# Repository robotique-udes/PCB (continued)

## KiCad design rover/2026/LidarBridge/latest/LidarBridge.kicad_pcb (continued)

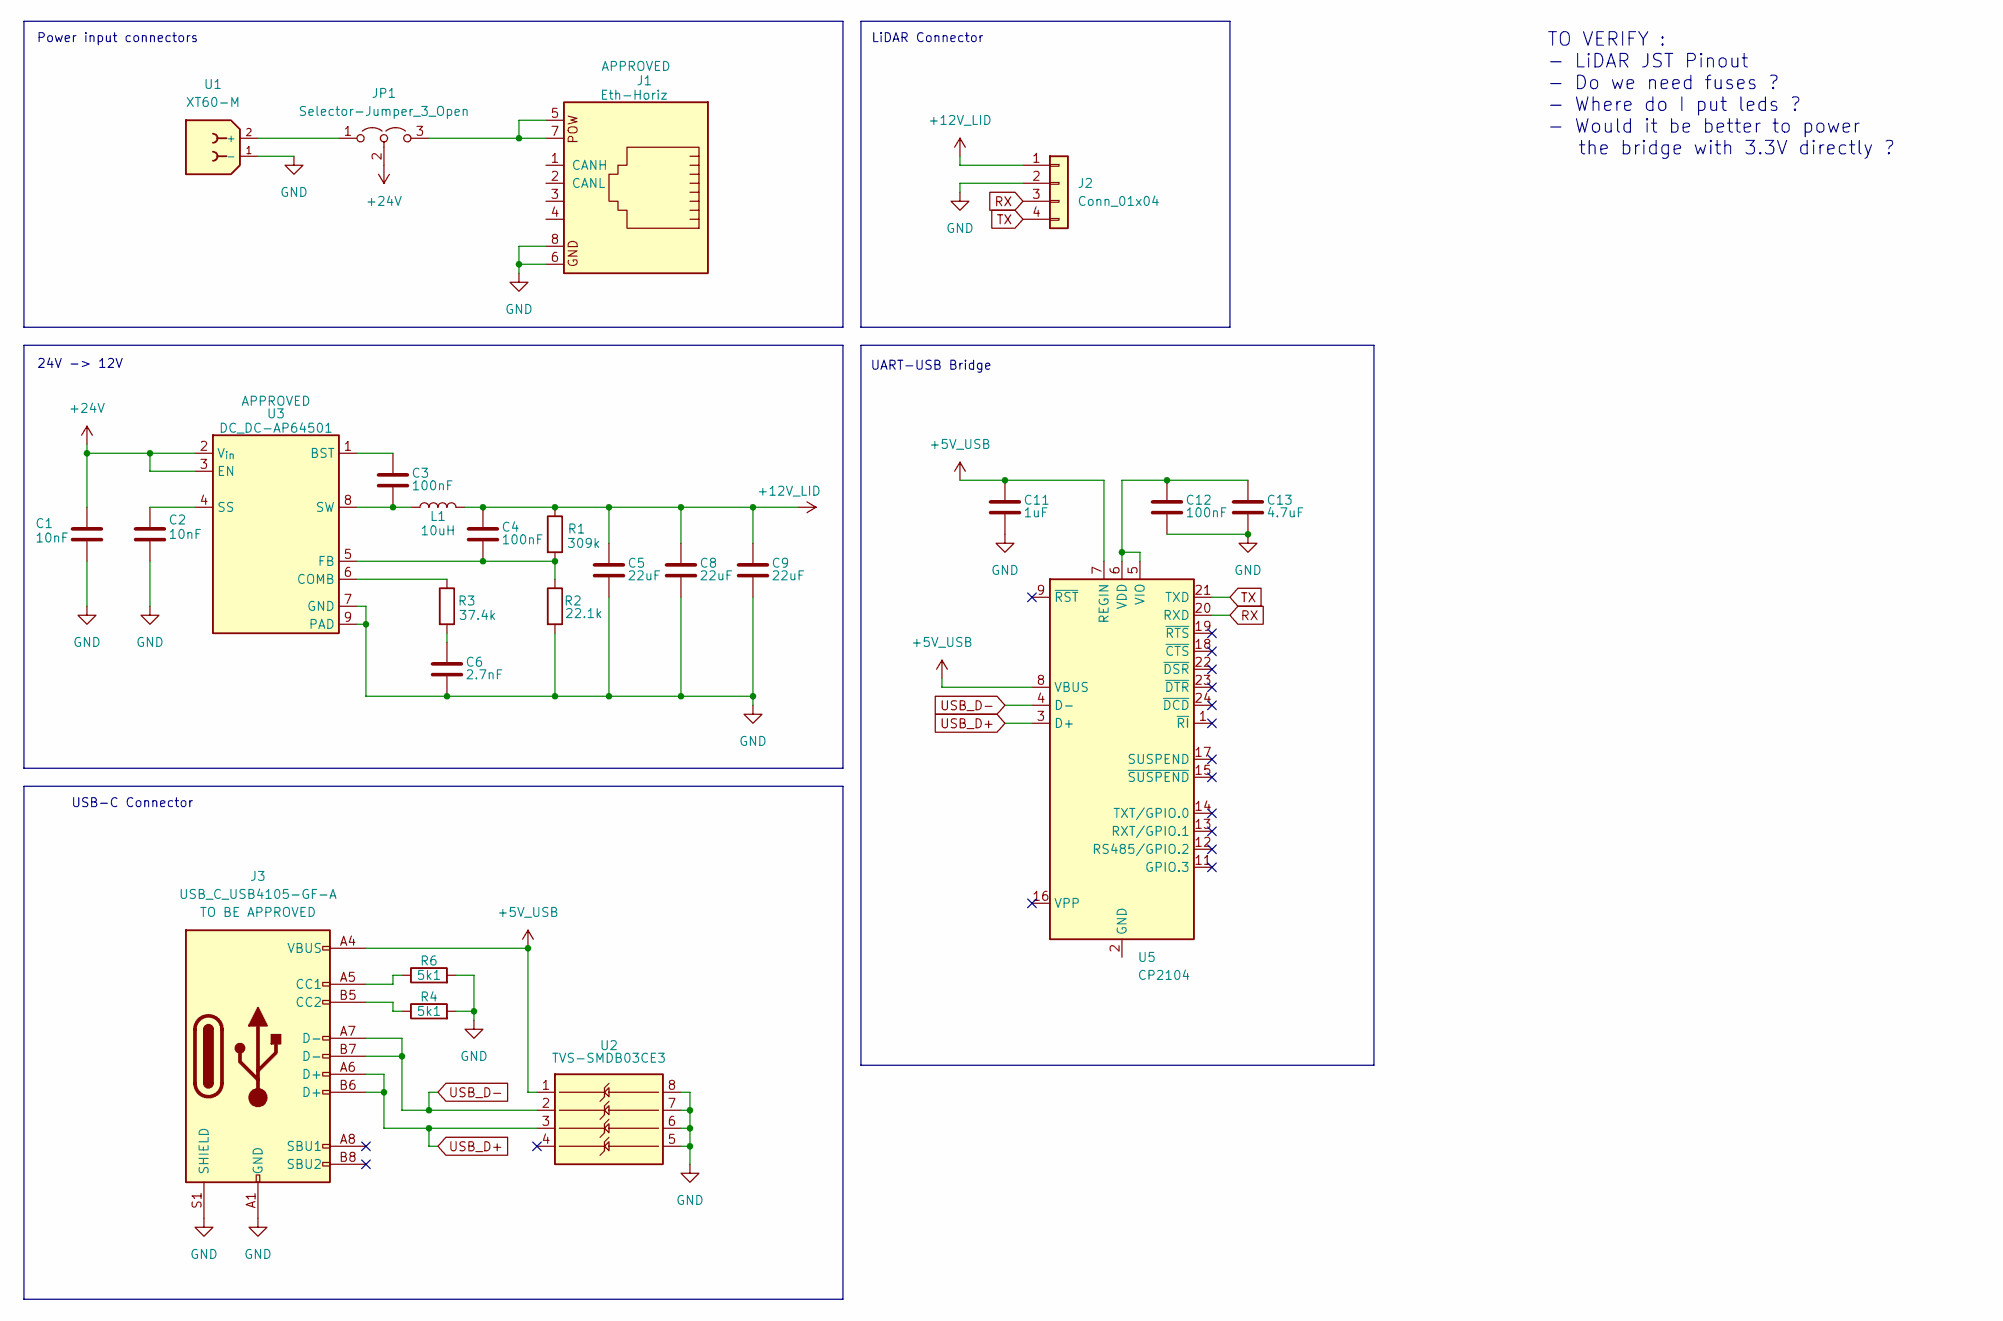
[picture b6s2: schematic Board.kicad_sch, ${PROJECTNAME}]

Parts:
C1, C2: 10nF; C_0805_2012Metric_Pad1.18x1.45mm_HandSolder
C3, C4, C12: 100nF; C_0805_2012Metric_Pad1.18x1.45mm_HandSolder
C5, C8, C9: 22uF; C_0805_2012Metric_Pad1.18x1.45mm_HandSolder
C6: 2.7nF; C_0805_2012Metric_Pad1.18x1.45mm_HandSolder
C11: 1uF; C_0805_2012Metric_Pad1.18x1.45mm_HandSolder
C13: 4.7uF; C_0805_2012Metric_Pad1.18x1.45mm_HandSolder
J1: Eth-Horiz; Ethernet_Horizontal
J2: Conn_01x04; JST_PH_B4B-PH-K_1x04_P2.00mm_Vertical
J3: USB_C_USB4105-GF-A; USB_C_Receptacle_GCT_USB4105-xx-A_16P_TopMnt_Horizontal
JP1: Selector-Jumper_3_Open; PinHeader_1x03_P2.54mm_Vertical
L1: 10uH; L_3.6u_ASPI-6045S-3R6N-T
R1: 309k; R_0805_2012Metric_Pad1.20x1.40mm_HandSolder
R2: 22.1k; R_0805_2012Metric_Pad1.20x1.40mm_HandSolder
R3: 37.4k; R_0805_2012Metric_Pad1.20x1.40mm_HandSolder
R4, R6: 5k1; R_0805_2012Metric_Pad1.20x1.40mm_HandSolder
U1: XT60-M; AMASS_XT60-M_1x02_P7.20mm_Vertical
U2: TVS-SMDB03CE3; SOIC-8_3.9x4.9mm_P1.27mm
U3: DC_DC-AP64501; SOIC-8-1EP_3.9x4.9mm_P1.27mm_EP2.29x3mm
U5: CP2104; QFN-24-1EP_4x4mm_P0.5mm_EP2.6x2.6mm

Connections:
+5V_USB: C11.1, J3.A4 (VBUS), J3.A9 (VBUS), J3.B4 (VBUS), J3.B9 (VBUS), U2.1, U5.7 (REGIN), U5.8 (VBUS)
+12V_LID: C4.1, C5.1, C8.1, C9.1, J2.1, L1.2, R1.1
+24V: C1.1, JP1.2 (C), U3.2 (V_{in}), U3.3 (EN)
GND: C1.2, C2.2, C5.2, C6.2, C8.2, C9.2, C11.2, C12.2, C13.2, J1.6, J1.8, J2.2, J3.A1 (GND), J3.A12 (GND), J3.B1 (GND), J3.B12 (GND), J3.S1 (SHIELD), R2.2, R4.2, R6.2, U1.1 (-), U2.5, U2.6, U2.7, U2.8, U3.7 (GND), U3.9 (PAD); also elsewhere on the board
unnamed: C6.1, R3.2
unnamed: J3.A5 (CC1), R6.1
unnamed: J3.B5 (CC2), R4.1
unnamed: JP1.1 (A), U1.2 (+)
unnamed: J1.5, J1.7, JP1.3 (B)
unnamed: C3.1, U3.1 (BST)
unnamed: R3.1, U3.6 (COMB)
unnamed: C4.2, R1.2, R2.1, U3.5 (FB)
unnamed: C2.1, U3.4 (SS)
unnamed: C3.2, L1.1, U3.8 (SW)
unnamed: U5.2 (GND), U5.25 (GND)
unnamed: C12.1, C13.1, U5.5 (VIO), U5.6 (VDD)
RX: J2.3, U5.20 (RXD)
TX: J2.4, U5.21 (TXD)
USB_D+: J3.A6 (D+), J3.B6 (D+), U2.3, U5.3 (D+)
USB_D-: J3.A7 (D-), J3.B7 (D-), U2.2, U5.4 (D-)

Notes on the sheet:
TO VERIFY : - LiDAR JST Pinout - Do we need fuses ? - Where do I put leds ? - Would it be better to power the bridge with 3.3V directly ?
LiDAR Connector
USB-C Connector
24V -> 12V
Power input connectors
UART-USB Bridge

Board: 4 copper layers, 30 parts (0 on the bottom side), 21 nets, no tracks yet.

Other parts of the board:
U2#2: CP2102N-Axx-xQFN24; QFN-24-1EP_4x4mm_P0.5mm_EP2.6x2.6mm

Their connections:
unnamed: U2#2.2 (GND), U2#2.25 (GND)

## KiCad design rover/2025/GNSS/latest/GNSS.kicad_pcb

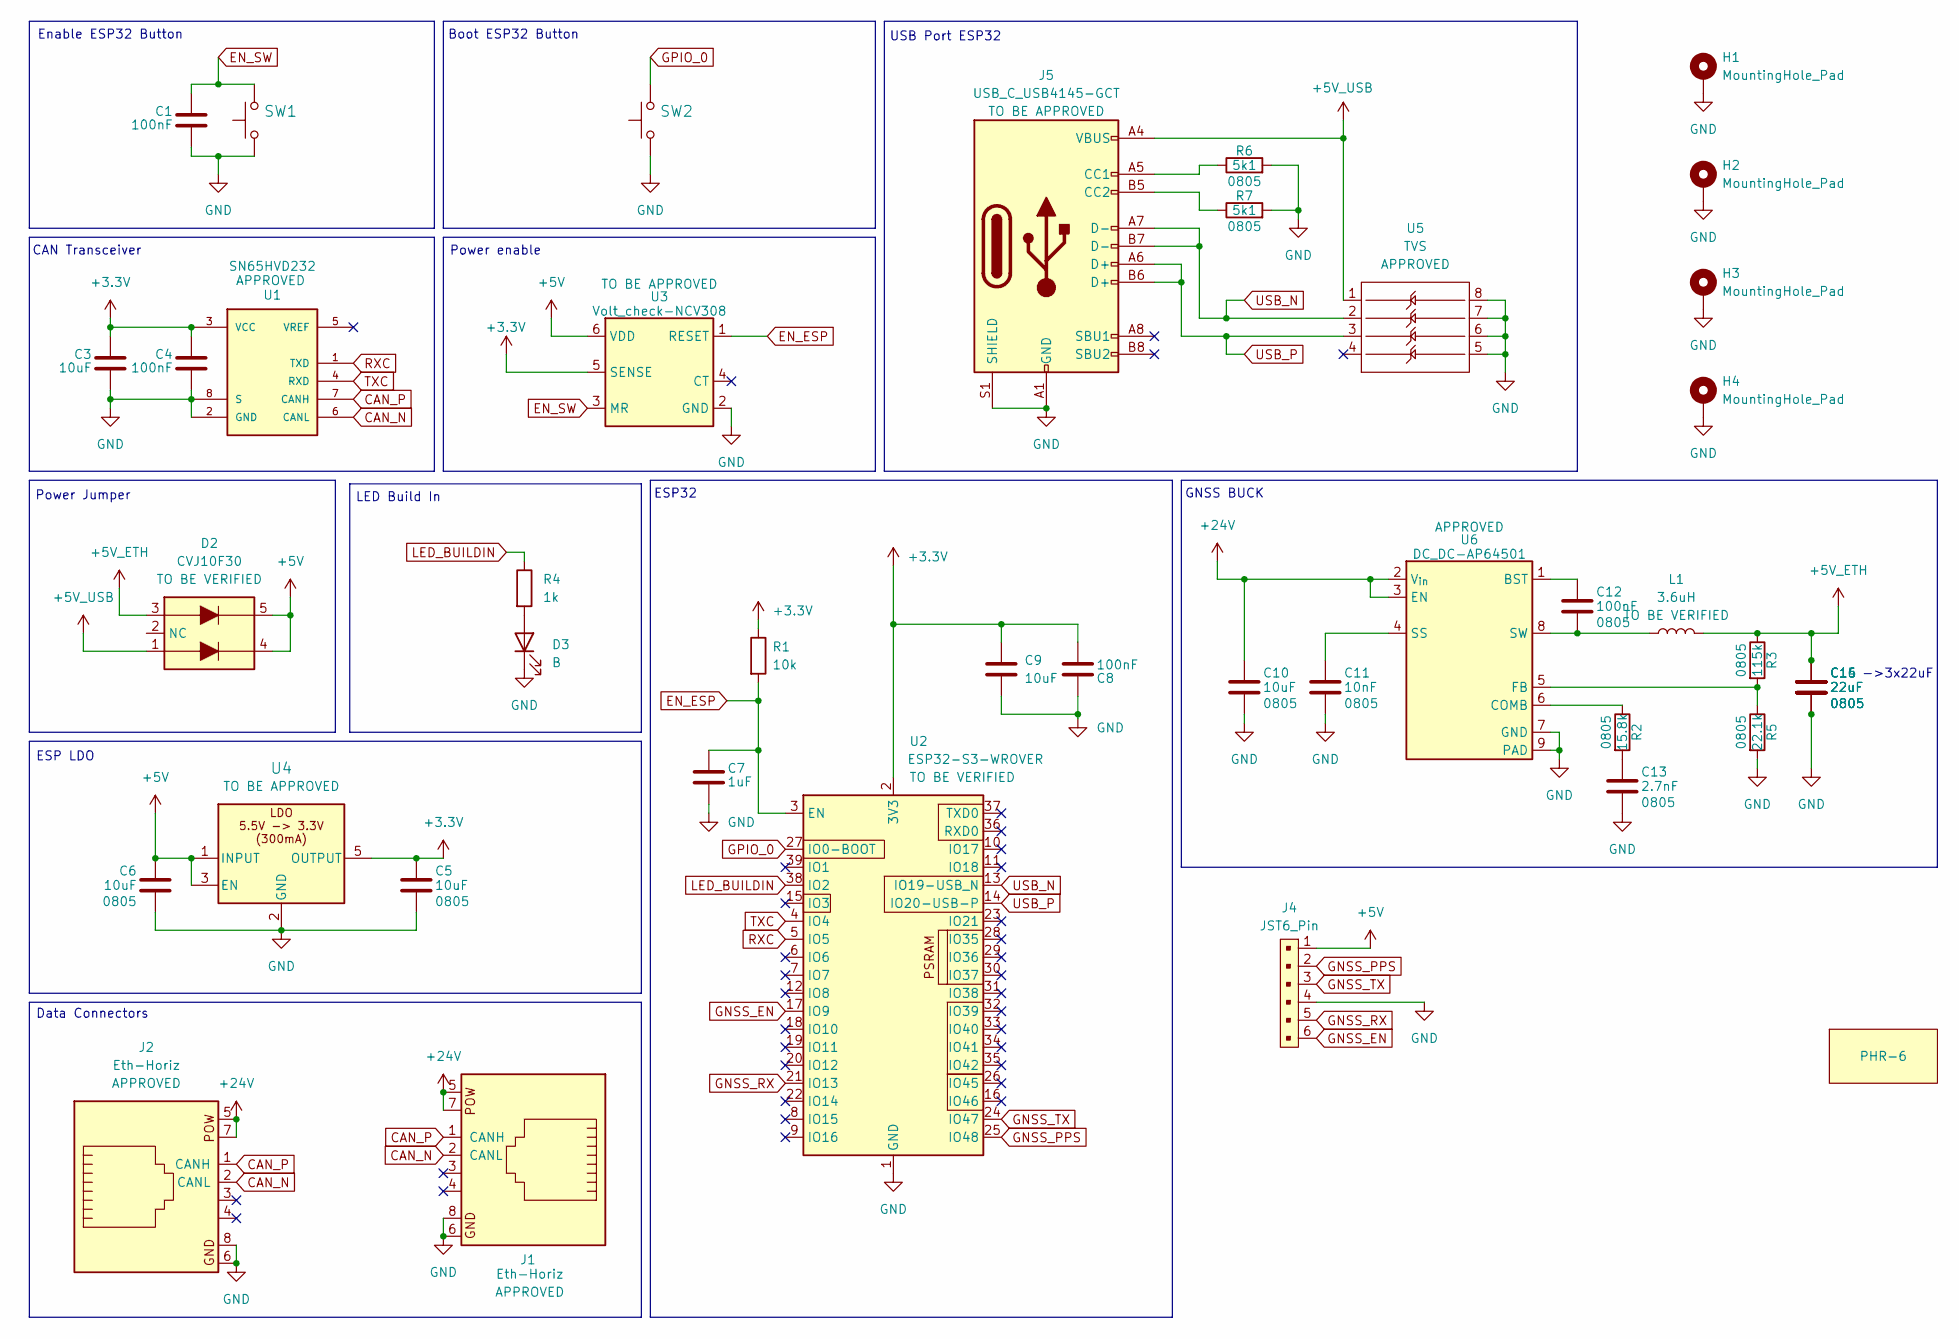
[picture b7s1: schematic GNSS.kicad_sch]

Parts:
C1, C4, C8, C12: 100nF; C_0805_2012Metric_Pad1.18x1.45mm_HandSolder
C3, C5, C6, C9, C10: 10uF; C_0805_2012Metric_Pad1.18x1.45mm_HandSolder
C7: 1uF; C_0805_2012Metric_Pad1.18x1.45mm_HandSolder
C11: 10nF; C_0805_2012Metric_Pad1.18x1.45mm_HandSolder
C13: 2.7nF; C_0805_2012Metric_Pad1.18x1.45mm_HandSolder
C14, C15, C16: 22uF; C_0805_2012Metric_Pad1.18x1.45mm_HandSolder
D2: CVJ10F30; Diode_schottky-CVJ10F30
D3: B; LED_0805_2012Metric_Pad1.15x1.40mm_HandSolder
G1: PHR-6
H1, H2, H3, H4: MountingHole_Pad; MountingHole_3.2mm_M3_DIN965_Pad_TopBottom
J1, J2: Eth-Horiz; Ethernet_Horizontal
J4: JST6_Pin; JST_PH_B6B-PH-K_1x06_P2.00mm_Vertical
J5: USB_C_USB4145-GCT; USB4145_GCT
L1: 3.6uH; L_3.6u_ASPI-6045S-3R6N-T
R1: 10k; R_0805_2012Metric_Pad1.20x1.40mm_HandSolder
R2: 15.8k; R_0805_2012Metric_Pad1.20x1.40mm_HandSolder
R3: 115k; R_0805_2012Metric_Pad1.20x1.40mm_HandSolder
R4: 1k; R_0805_2012Metric_Pad1.20x1.40mm_HandSolder
R5: 22.1k; R_0805_2012Metric_Pad1.20x1.40mm_HandSolder
R6, R7: 5k1; R_0805_2012Metric_Pad1.20x1.40mm_HandSolder
SW1, SW2: SW-PTS815SJM250SMTRLFS; SW-PTS815 SJM250SMTRLFS
U1: SN65HVD232; SOIC-8_3.9x4.9mm_P1.27mm; PARTREV 4
U2: ESP32-S3-WROVER; ESP32-S3-WROOM-1U
U3: Volt_check-NCV308; TSOP-6_1.65x3.05mm_P0.95mm
U4: LDO-TLV74033PDBVR; SOT-23-5_HandSoldering
U5: TVS; SOIC-8_3.9x4.9mm_P1.27mm
U6: DC_DC-AP64501; SOIC-8-1EP_3.9x4.9mm_P1.27mm_EP2.29x3mm

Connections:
+3.3V: C3.1, C4.1, C5.1, C8.2, C9.1, R1.1, U1.3 (VCC), U2.2 (3V3), U3.5 (SENSE), U4.5 (OUTPUT)
+5V: C6.1, D2.4, D2.5, J4.1, U3.6 (VDD), U4.1 (INPUT), U4.3 (EN)
+5V_ETH: C14.1, C15.1, C16.1, D2.3, L1.2, R3.1
+5V_USB: D2.1, J5.A4 (VBUS), J5.A9 (VBUS), J5.B4 (VBUS), J5.B9 (VBUS), U5.1
+24V: C10.1, J1.5, J1.7, J2.5, J2.7, U6.2 (V_{in}), U6.3 (EN)
CAN_N: J1.2 (CANL), J2.2 (CANL), U1.6 (CANL)
CAN_P: J1.1 (CANH), J2.1 (CANH), U1.7 (CANH)
EN_ESP: C7.1, R1.2, U2.3 (EN), U3.1 (RESET)
EN_SW: C1.1, SW1.4, U3.3 (MR)
GND: C1.2, C3.2, C4.2, C5.2, C6.2, C7.2, C8.1, C9.2, C10.2, C11.2, C13.2, C14.2, C15.2, C16.2, D3.1 (K), H1.1, H2.1, H3.1, H4.1, J1.6, J1.8, J2.6, J2.8, J4.4, J5.A1 (GND), J5.A12 (GND), J5.B1 (GND), J5.B12 (GND), J5.S1 (SHIELD), R5.2, R6.2, R7.2, SW1.1, SW1.2, SW2.1, SW2.2, U1.2 (GND), U1.8 (S), U2.1 (GND), U2.40 (GND), U2.41 (GND), U3.2 (GND), U4.2 (GND), U5.5, U5.6, U5.7, U5.8, U6.7 (GND), U6.9 (PAD)
GNSS_EN: J4.6, U2.17 (IO9)
GNSS_PPS: J4.2, U2.25 (IO48)
GNSS_RX: J4.5, U2.21 (IO13)
GNSS_TX: J4.3, U2.24 (IO47)
GPIO_0: SW2.4, U2.27 (IO0-BOOT)
LED_BUILDIN: R4.1, U2.38 (IO2)
unnamed: C13.1, R2.2
unnamed: D3.2 (A), R4.2
unnamed: J5.A5 (CC1), R6.1
unnamed: J5.B5 (CC2), R7.1
unnamed: C12.1, U6.1 (BST)
unnamed: R2.1, U6.6 (COMB)
unnamed: R3.2, R5.1, U6.5 (FB)
unnamed: C11.1, U6.4 (SS)
unnamed: C12.2, L1.1, U6.8 (SW)
RXC: U1.1 (TXD), U2.5 (IO5)
TXC: U1.4 (RXD), U2.4 (IO4)
USB_N: J5.A7 (D-), J5.B7 (D-), U2.13 (IO19-USB_N), U5.2
USB_P: J5.A6 (D+), J5.B6 (D+), U2.14 (IO20-USB-P), U5.3

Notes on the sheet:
Enable ESP32 Button
Power enable
->3x22uF
Data Connectors
Boot ESP32 Button
LED Build In
ESP32
CAN Transceiver
ESP LDO
GNSS BUCK
Power Jumper
USB Port ESP32

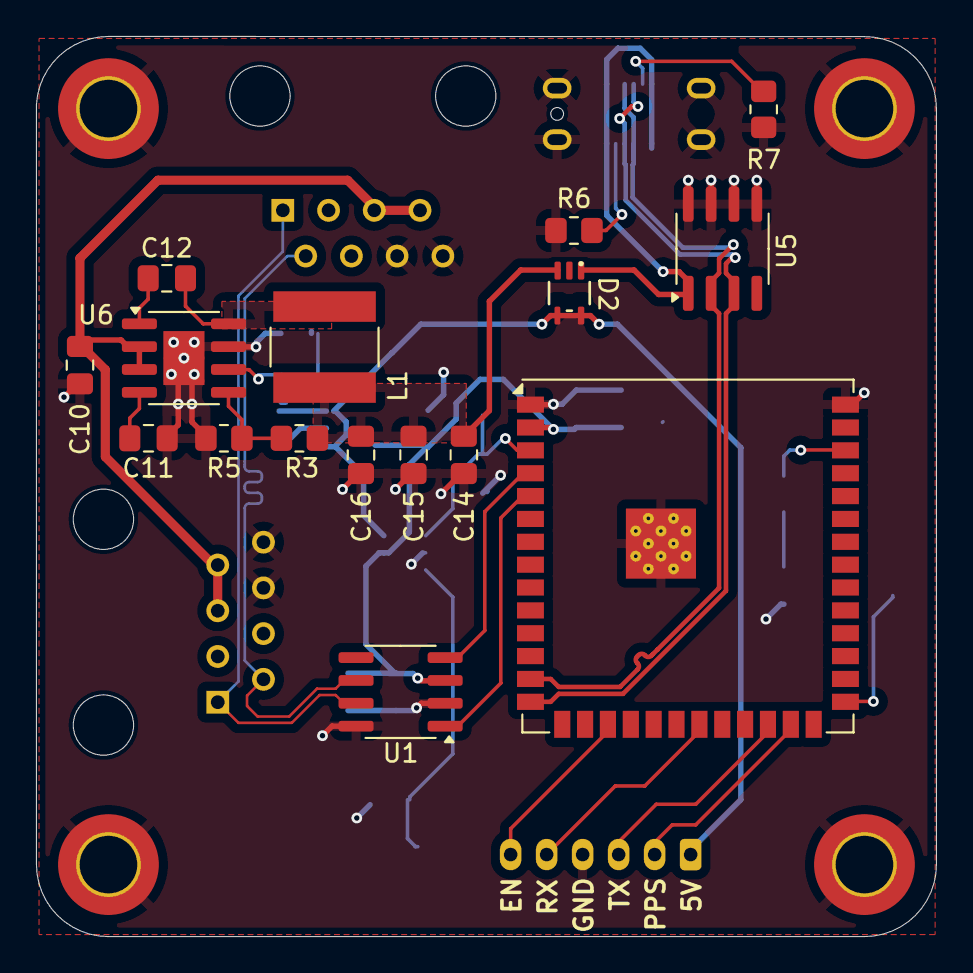
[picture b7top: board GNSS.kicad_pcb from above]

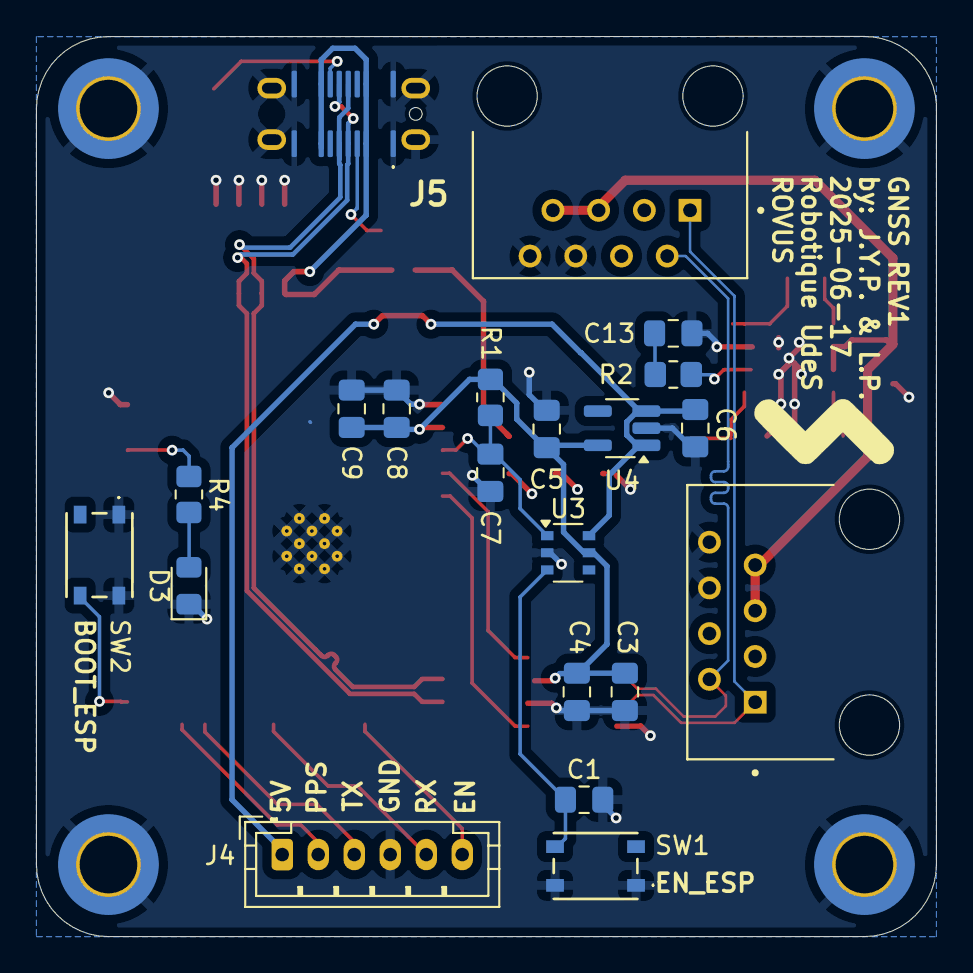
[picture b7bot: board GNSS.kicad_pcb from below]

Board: 4 copper layers, 50.0 x 50.0 mm, 41 parts (21 on the bottom side), 29 nets.

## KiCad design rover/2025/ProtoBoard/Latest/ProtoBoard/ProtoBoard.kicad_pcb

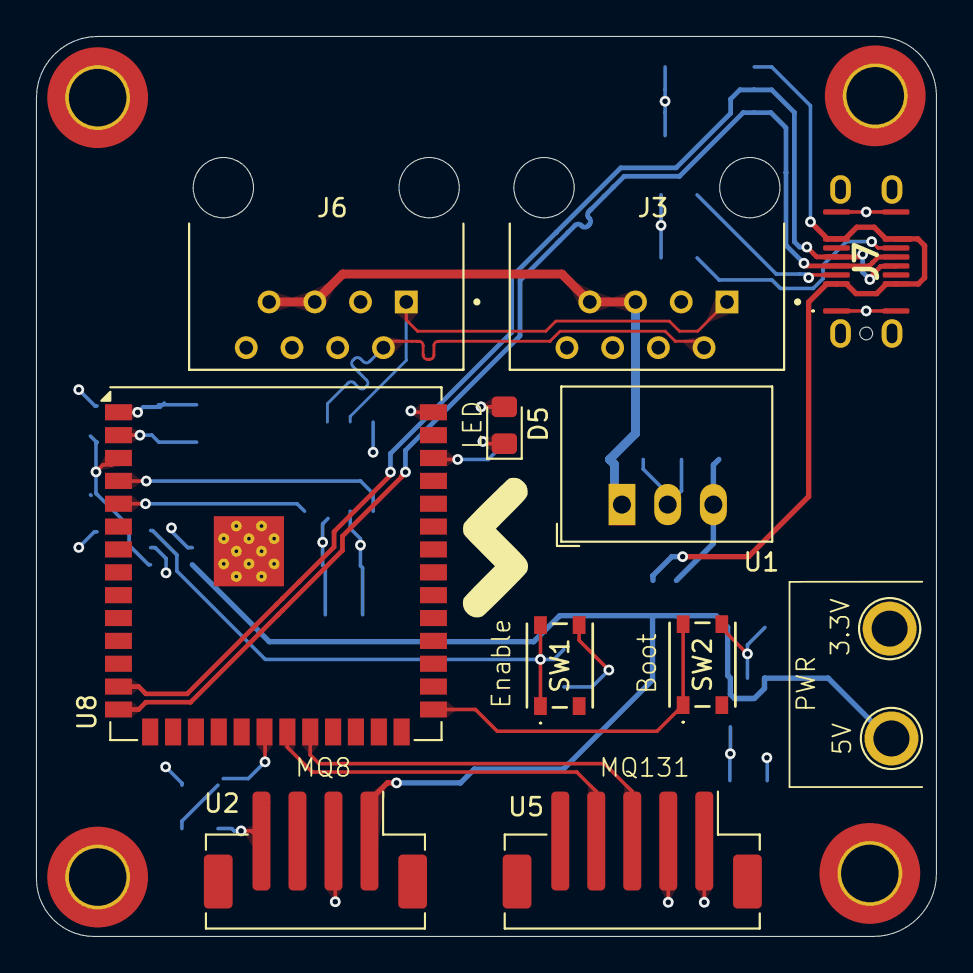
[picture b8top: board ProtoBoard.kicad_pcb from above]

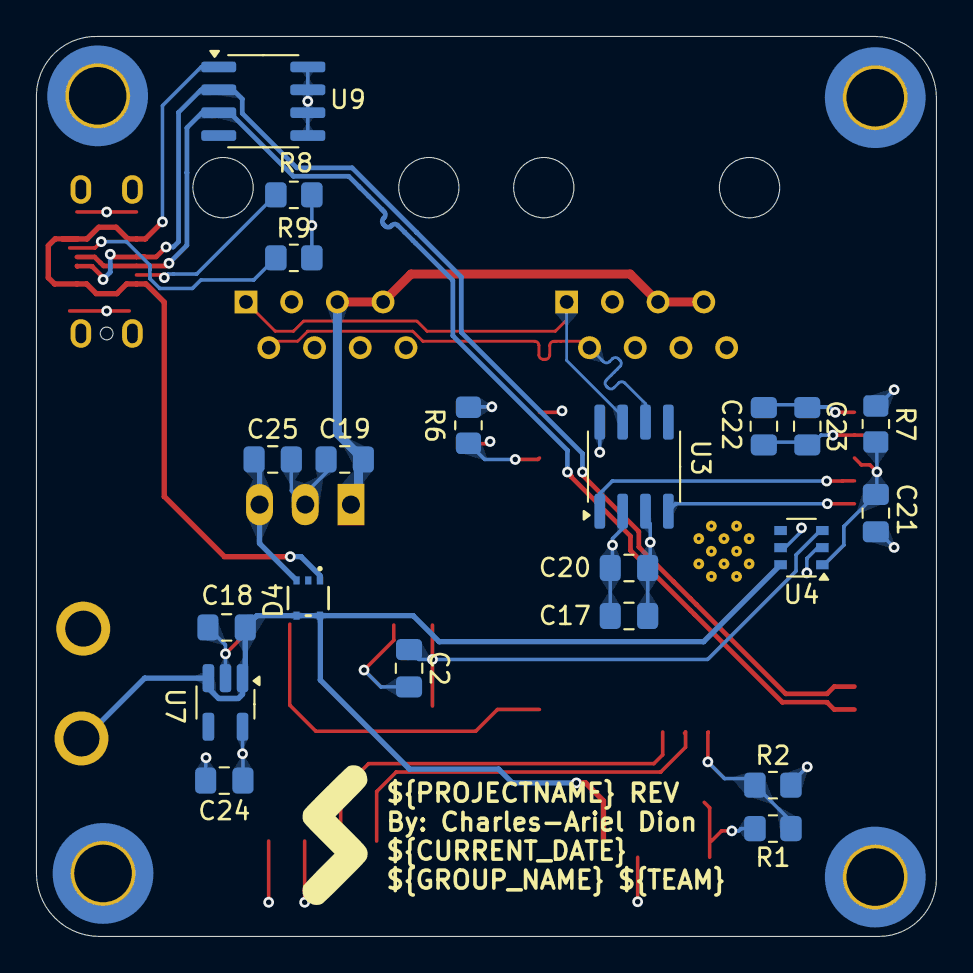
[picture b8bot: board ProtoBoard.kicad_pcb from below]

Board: 4 copper layers, 50.0 x 50.0 mm, 37 parts (21 on the bottom side), 23 nets.

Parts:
C2, C20, C23: 100nF; C_0805_2012Metric_Pad1.18x1.45mm_HandSolder
C17, C18, C19, C22, C24, C25: 10uF; C_0805_2012Metric_Pad1.18x1.45mm_HandSolder
C21: 1uF; C_0805_2012Metric_Pad1.18x1.45mm_HandSolder
D4: CVJ10F30; Diode_schottky-CVJ10F30
D5: B; LED_0805_2012Metric_Pad1.15x1.40mm_HandSolder
H9, H10, H11, H12: MountingHole_Pad; MountingHole
J3, J6: Eth-Horiz; Ethernet_Horizontal
J7: USB_C_USB4145-GCT; USB4145_GCT
R1, R7: 10k; R_0805_2012Metric_Pad1.20x1.40mm_HandSolder
R2: 20k; R_0805_2012Metric_Pad1.20x1.40mm_HandSolder
R6: 1k; R_0805_2012Metric_Pad1.20x1.40mm_HandSolder
R8, R9: 5k1; R_0805_2012Metric_Pad1.20x1.40mm_HandSolder
SW1, SW2: SW-PTS815SJM250SMTRLFS; SW-PTS815 SJM250SMTRLFS
TP1, TP2: TestPoint; TestPoint_Plated_Hole_D2.0mm
U1: R-78E5.0-0.5; Converter_DCDC_RECOM_R-78E-0.5_THT
U2: MQ-8; JST_PH_B4B-PH-SM4-TB_1x04-1MP_P2.00mm_Vertical
U3: SN65HVD232; SOIC-8_3.9x4.9mm_P1.27mm
U4: Volt_check-NCV308; TSOP-6_1.65x3.05mm_P0.95mm
U5: MQ-131; JST_PH_B5B-PH-SM4-TB_1x05-1MP_P2.00mm_Vertical
U7: LDO-TLV74033PDBVR; SOT-23-5_HandSoldering
U8: ESP32-S3-WROVER; ESP32-S3-WROOM-1U
U9: TVS; SOIC-8_3.9x4.9mm_P1.27mm

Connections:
+3.3V: C17.1, C20.1, C22.1, C23.2, C24.1, R7.1, TP2.1, U3.3 (VCC), U4.5 (SENSE), U5.1 (3.3V), U7.5 (OUTPUT), U8.2 (3V3)
+5V: C18.1, D4.4, D4.5, TP1.1, U2.1 (5V), U4.6 (VDD), U7.1 (INPUT), U7.3 (EN)
+5V_ETH: C25.1, D4.3, U1.3 (OUT)
+5V_USB: D4.1, J7.A4 (VBUS), J7.A9 (VBUS), J7.B4 (VBUS), J7.B9 (VBUS), U9.1
+24V: C19.1, J3.5, J3.7, J6.5, J6.7, U1.1 (IN)
/Sensors/MQ8_AOUT_5V: R1.1 (+), U2.4 (A0)
CAN_N: J3.2 (CANL), J6.2 (CANL), U3.6 (CANL)
CAN_P: J3.1 (CANH), J6.1 (CANH), U3.7 (CANH)
EN_ESP: C21.1, R7.2, U4.1 (RESET), U8.3 (EN)
EN_SW: C2.1, SW1.1, SW1.2, U4.3 (MR)
GND: C2.2, C17.2, C18.2, C19.2, C20.2, C21.2, C22.2, C23.1, C24.2, C25.2, D5.1 (K), H9.1, H10.1, H11.1, H12.1, J3.6, J3.8, J6.6, J6.8, J7.A1 (GND), J7.A12 (GND), J7.B1 (GND), J7.B12 (GND), J7.S1 (SHIELD), R2.2 (-), R8.2, R9.1, SW1.4, SW2.4, U1.2 (GND), U2.2 (GND), U3.2 (GND), U3.8 (S), U4.2 (GND), U5.2 (GND), U7.2 (GND), U8.1 (GND), U8.40 (GND), U8.41 (GND), U9.5, U9.6, U9.7, U9.8
GPIO_0: SW2.1, SW2.2, U8.27 (IO0-BOOT)
LED_BUILDIN: R6.1, U8.38 (IO2)
MQ8_AOUT: R1.2 (-), R2.1 (+), U8.20 (IO12)
MQ131_SCL: U5.4 (SCL), U8.21 (IO13)
MQ131_SDA: U5.3 (SDA), U8.22 (IO14)
unnamed: D5.2 (A), R6.2
unnamed: J7.A5 (CC1), R8.1
unnamed: J7.B5 (CC2), R9.2
RXC: U3.1 (TXD), U8.4 (IO4)
TXC: U3.4 (RXD), U8.5 (IO5)
USB_N: J7.A7 (D-), J7.B7 (D-), U8.13 (IO19-USB_N), U9.2
USB_P: J7.A6 (D+), J7.B6 (D+), U8.14 (IO20-USB-P), U9.3

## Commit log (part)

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2024-03-26 init commit
2024-03-26 Started routing
2024-03-27 Final V1 version, ready to order
2024-03-30 New Can bus termination PCB
2024-04-01 Finalized terminason pcb
2024-04-03 rovus esp32-s3 devkit + gps module
2024-04-03 Fix wrong file name
2024-04-03 Renamed
2024-04-03 Shield Drive Moteur DC
2024-04-04 modif
2024-04-07 boms
2024-04-08 Auto stash before merge of "main" and "origin/main"
2024-04-10 no msg
2024-04-14 Start of PDB
2024-04-15 pdb pcb
2024-04-16 PDB routing
2024-04-18 fix terminaison
2024-04-18 Compass PCB
2024-04-18 gerber
2024-04-20 pcb j0 + j1
2024-04-21 final j0 + j1 drive
2024-04-22 PCB bras j2
2024-04-23 Generated BOM
2024-04-24 BOM + schema
2024-04-24 Updated wrong footprint in rocker splitter
2024-04-30 export pdb step
2024-05-16 new driver to replace talon srx
2024-05-17 rev2 of arm
2024-05-17 final of REV0
2024-06-11 New splitter
2024-06-25 drive pince
2024-06-26 rev1 of RockerSplitter
2024-06-26 rev3 drive27A
2024-06-26 edge cut adjustement
2024-07-01 j2,3,4
2024-07-01 redone arm drive with 24V input + fuse
2024-07-01 REV1 - j3,4,5
2024-07-01 fuse j2 drive + 24v ldo
2024-07-02 RockerSplitter current rating adjustement
2024-07-02 RockerSplitterV2 Rev2
2024-07-02 Drive27A Thermal design validation
2024-07-03 ArmDrive J0+J1 Thermal design validation
2024-07-03 ArmDrive J2 Thermal design validation
2024-07-03 ArmDrive_J3_4_J5
2024-07-07 arm drive JL done
2024-07-07 arm drive JL export files
2024-07-08 pcb science in progress
2024-07-09 science almost done
2024-07-09 science: layout done missing silk layer
2024-07-10 Science: done
2024-07-10 new 3d rockersplitter
2024-07-19 rev3 rockersplitter in progress
2024-07-19 REV3 Rocker splitter
2024-07-19 added fuse 3d on j3,4,5
2024-07-24 new drive 27A
2024-07-25 Ajout PCB Antenne
2024-07-25 Ajout de la V1 du PCB Antenna dans .../antenna
2024-07-26 fix gpio39 on j3_4_5
2024-09-18 Create README.md
    Ajout d'un README.md
2024-09-26 Create README.md
    template de README pour la terminaison can
2024-09-30 Cleanup + review
2024-10-03 Update README.md
    README pas finit.
2024-10-10 Created exo repo
2024-10-19 Add docs 2023-2025
2024-10-19 Commented most projects
2024-10-19 changement de nom
2024-10-23 Create README.md
    Copié ce que j'avais écrit dans la branche rover/doc_review
2024-10-24 Fichier de fab Drive_27A
    Génération des fichier de fabrication pour la Drive_27A
2024-10-24 Update .gitignore
    Retirer le suivi de tous les dossiers de bachup de kicad (*-backups/),
    de .DS_Store,
    et de tous les fichiers de fabrications gerber
2024-10-24 Supression de fichiers du .gitignore
    Fichier de fabrication
    Fichiers de Backups
    Fichiers .DS_Store
2024-10-25 Add file of the moustache
2024-10-30 Created motherboard project
2024-10-31 Premier Jet
2024-11-06 V2.1 du BNOV
    version préliminaire du BNOV2.
2024-11-06 Version préliminaire du BNOV
2024-11-07 changement moustahce
2024-11-13 ush moustache
2024-11-19 BNOV2 V0.2
2024-11-21 update step
2024-11-22 Changement BNO et moustache
2024-11-28 Edit switched power pins
2024-11-28 Ajout des composants pour la majorité des PCBs
2024-11-29 Now support 5v to 24v input from eth connector
2024-12-04 Ajout du port USB C
2024-12-05 Ajoute de 3d model pour le esp32
2024-12-06 Reorg
2024-12-06 Revert "Reorg"
    This reverts commit fb8e8e68ef64dce77992aad18266337ef025036d.
2024-12-06 Moved still used project in 2025
2024-12-06 New pdb project + lib changes
2024-12-10 Modif des PN JLCPCB dans Drive_27A
2024-12-16 Add STATUS column
2024-12-18 PDB progress
2024-12-26 Push BNO et Moustache Gerber
2024-12-30 push schema électrique
2024-12-30 2nd push whoopsie
2024-12-31 ajout infromation et d'épaisseur des traces selon le netclass et de joli couleur hehe
2025-01-03 Commencement de la section I2C du PCB
2025-01-03 Refaire le circuit I2C différentiel
2025-01-03 Commencement du circuit 3.3V
2025-01-13 Start of PDB layout
2025-01-13 ajout du uSD,USBC et du connecteur
2025-01-14 PDB V0
2025-01-14 Changed name + silkscreen DDB
2025-01-15 Modif lib pins
    modification des types de pins pour réduire les erreurs pour que ça soit utile d'utiliser le ERC
2025-01-15 add Rover Ethernet Switch + Rover Servo Controller
2025-01-16 Small 5A regulator pcb
2025-01-17 ajout USB-C, microSD et connecteur
2025-01-18 Alimentaation quasi fini
2025-01-18 Quelque détail
2025-01-21 ajout CAN
2025-01-21 Add dels
2025-01-21 LED Footprint
2025-01-22 Modif nom library
    Pour que la lib s'affiche en premier
2025-01-22 Update DDB Link to lib
2025-01-22 Update sch and pcb for correct link
2025-01-22 Update DDB
    sch and pcb for correct link
2025-01-22 Revert "Modif nom library"
    This reverts commit e4e2711b1b2705a504d96139028ca170ed6eba46.
2025-01-22 Multiple changes to lib + added + fixed pins ERC checks
2025-01-22 Resistor and Cap 0805
2025-01-23 Revert "Resistor and Cap 0805"
    This reverts commit 67557315c082f03d933c910415aa55c0264a018f.
2025-01-23 R and CAP of multiple sizes
    0805 0603 1206
2025-01-28 selector schematic done, needs checkup
2025-01-29 Reversed switch holder
2025-02-03 DDB REV 0 done
2025-02-04 POTENC PCB Done
2025-02-04 Start of ARM_JL
2025-02-05 Selector changes
2025-02-05 Update Selector Lib Ref
2025-02-05 ARM-JL
2025-02-05 selector layout
2025-02-05 ARM-JL Drawing Done
2025-02-05 ARM-JL Routing in progress
2025-02-06 Add JST2 pin
2025-02-06 Début de PCB HighAmp
    J'aime la vie
2025-02-06 Add jst 4 pins
2025-02-06 JST: Change JST 2 pin
    Using the RoverLib One
2025-02-06 Selector: remove R5
2025-02-06 PCB GNSS
2025-02-06 Remove PCB documentation
2025-02-06 ARM-JL REV0 done
2025-02-06 Power source jumper connections changed
2025-02-07 Renaming + reorganisation of 2025 project for new standard
2025-02-08 Start of template
2025-02-08 Update_HighAmpOut_2025-02-08
    Avancement de la shématique
2025-02-08 Adding all the drive_J2 files
2025-02-08 drive j2 lib modifications
2025-02-08 Design review
2025-02-09 Template done
2025-02-09 template
2025-02-09 Project Template
2025-02-09 small selector updates
2025-02-09 Final modifications (DriveJ2)
2025-02-09 Update Mounting Hole
2025-02-09 selector layout updates
2025-02-12 Selector ready for update
2025-02-12 Cleanup PCBs pour convensions
2025-02-12 Changing path to library
2025-02-12 selector done
2025-02-12 Modify lib table of selector
2025-02-13 Update kicad lib
2025-02-14 Last touch before order for ARMJL, Regulator and DDB + start of J345
2025-02-15 Final changes on connector + cleaning directory
2025-02-16 Avancement PCB HighAmp
2025-02-16 Avancement PCB HighAmpOutput
2025-02-17 Upgraded version of DriveJ2
2025-02-17 PCB HighAmpOutput version final
    Devrais être la version final.
2025-02-17 Correction PCB HighAmpOutput
2025-02-18 ArmJ345 routing
2025-02-18 Approving some Footprint
2025-02-18 Selector PCB update footprints
2025-02-19 Selector: Correction symboles
2025-02-19 ARMJ345 V0 done
2025-02-19 Rev1 pcb gnss
    Je vais changer le schematic pour qu'il match le template plus tard.
2025-02-19 Done
2025-02-19 Pcb gnss ground planes manquantes ajoutées
2025-02-19 Selector Revision
2025-02-19 ArmJ345 Revision
2025-02-19 Plane modification for amp rating
2025-02-19 J345 Fix
2025-02-19 GNSS Revision (Pas finit)
2025-02-19 Off board connections + silkscreen
2025-02-19 ArmJ2 revised for order
2025-02-19 Regulator Ready to order
2025-02-19 Selector JST PH connectors
2025-02-19 script for auto bom
2025-02-19 GNSS Petits changements
    Jacob était à côté de moi quand j'ai ouvert le pcb et il m'a aidé.
    - Skew dans les traces différentielles USB et CAN réglé.
    - Pour le USB, une des deux traces différentielles doit passer à travers des vias afin de swap les deux signaux de côté. Donc, la trace qui ne passe pas par des vias est une épaisseur de board plus l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
    - Texte pour le connecteur de GNSS flippé pour qu'il soit du bon sens
    - Traces 24V de CAN élargies de 12 mil à 15 mil
    - Ajout d'un condensateur de sortie de 100nF au LDO 35-5 (U3)
2025-02-19 J'avais oublié de re-build les ground planes après mes modifs
2025-02-19 Exports + template modifs
2025-02-19 Gnss condo modifs
2025-02-19 REV GNSS et HAOutput
2025-02-19 Footprint
2025-02-19 Revert "REV GNSS et HAOutput"
    This reverts commit 5d427d660c4e7a301930cd61c736d2448627e1ac.
2025-02-19 HighAmp generated
2025-02-20 Ordering pcbs
2025-02-20 PCBs ordered
2025-02-22 comm_bms
2025-02-23 Comm_bms2
2025-02-28 Little update
2025-03-06 ROUTING FINIIII
2025-03-06 with some modif
2025-03-11 Retrait des vieilles pieces
    Boutons 2 pins, Connecteurs JST
2025-03-11 Suppress jst footprints ans adding mounting hole
2025-03-13 Flip RJ45
    Les RJ45 à sont rendus sur l'autre face du PCB pour le rendre moins épais. Les paires différentielles ont été reroute et le transceiver à été bougé pour être plus près.
    Le PCB est toujours pas refait selon le template
2025-03-13 gnss text update
2025-03-15 HighAMP_Rch_ADD_to_INPUT_to_7004
2025-03-18 Small correction on DDB
2025-03-19 Changé position bouton pour que ça rentre dans le casing
2025-03-27 Update
    update pour préparer pour la V2
2025-03-29 update_v2_highampoutput
2025-03-31 ADD_document
    add_doucment_deTest_pour_V2Highamp
2025-04-03 PCB connecteur pour les moteurs
2025-04-04 ouep
2025-04-11 Changed 3.3V led color
2025-04-11 fix for rev1
2025-04-13 Generated layer files
2025-04-17 Green LED for ArmJL 3V
2025-04-18 armj345 fixes
2025-04-19 Layout armj345
2025-04-20 commBMS modif
2025-04-21 push updates
2025-04-21 CONNECTOR PUSH
2025-04-22 push connecteur FIX
2025-04-27 DDB V2
2025-04-27 can routing not optimal
2025-04-27 V2_UPdate_HighAMP
2025-04-27 Exported CommBMS for order
2025-04-27 HighAmpOutput export
2025-04-28 Exported J345 for order
2025-04-28 DDB thermal relief and designator
2025-04-28 DDB: Fixed high current traces width + exported for order REV1
2025-04-28 BOM digikey
2025-04-30 Add_PCB_SETTING_DESCRIPTION_HighAmpOutput
2025-04-30 push pcb alim + moteurs
2025-04-30 push avec mesure
2025-05-08 Add files via upload
    update servo controller files
2025-05-08 update pdf servo controller
2025-05-20 DDB schematic
2025-05-25 Correction_ERR_PCB_HighAmpOutput
    L'erreur des mauvaises largeur des freins thermique à été corriger (on maintenant: 2 mm). De plus, la description du PCB à été effectuer.
2025-06-14 GNSS power bug fix
2025-06-14 gnss some more update
2025-06-17 gnss modif
2025-06-26 Creat project folder from template
2025-06-26 Esp+Pwr_Added
2025-07-04 gnss update
2025-07-06 PCB finit
    A faire approuver au besoin
2025-07-06 tit modif
2025-07-06 update gnss
2025-07-07 gnss rev1 commande
2025-07-09 PCB GAS Version 2 (compact) finit!
2025-07-10 PCB avec bug fixed
2025-07-10 Clean up pcb
2025-07-10 Rounded corners
2025-07-15 gas conn board
2025-07-17 Creation projet pour ProtoBoard
2025-07-17 Commencement du board + recherche
2025-08-11 footprint update
2025-10-02 edit
2025-10-04 initial project creation
2025-10-04 block diagram
2025-10-04 added todo
2025-10-04 updated todo
2025-10-04 DC-DC wiring
2025-10-05 schematic done
2025-10-08 leds
2025-10-08 PCB review
2025-10-08 Added image of pinout
2026-01-06 Clean up des branches exos
2026-01-06 Mise à jour du schéma électrique MoBoV2.1
2026-01-06 Clean up MoBo V2 et V2-1
2026-03-01 Pushing changed files
    multiple correctiosn done especially a new Mobo
2026-03-11 Added 10A buck
2026-03-16 Change name of a file that block cloning on windows
2026-03-18 bom html
2026-05-29 added v2 science module 2026
2026-05-29 fixed folder
2026-06-16 Finished pcb layout for science module waiting on first review
